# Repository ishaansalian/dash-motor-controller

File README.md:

# 48V BLDC Motor Controller for Dash Robot
Motor control PCB for the Dash humanoid robot project.

## Specs
- 48V nominal input
- 3-phase BLDC motor control
- DRV8323 gate driver
- CAN bus communication
- Based on Ben Katz + mjbots Moteus designs

## Status
🚧 In development - schematic complete, layout in progress

## Hardware
- MCU: STM32F446
- Gate Driver: DRV8323RSRGZT
- MOSFETs: BSC030N08NS5 (80V, 3mΩ)
- Encoder: MA732GQ-Z
- CAN: MCP2542FD

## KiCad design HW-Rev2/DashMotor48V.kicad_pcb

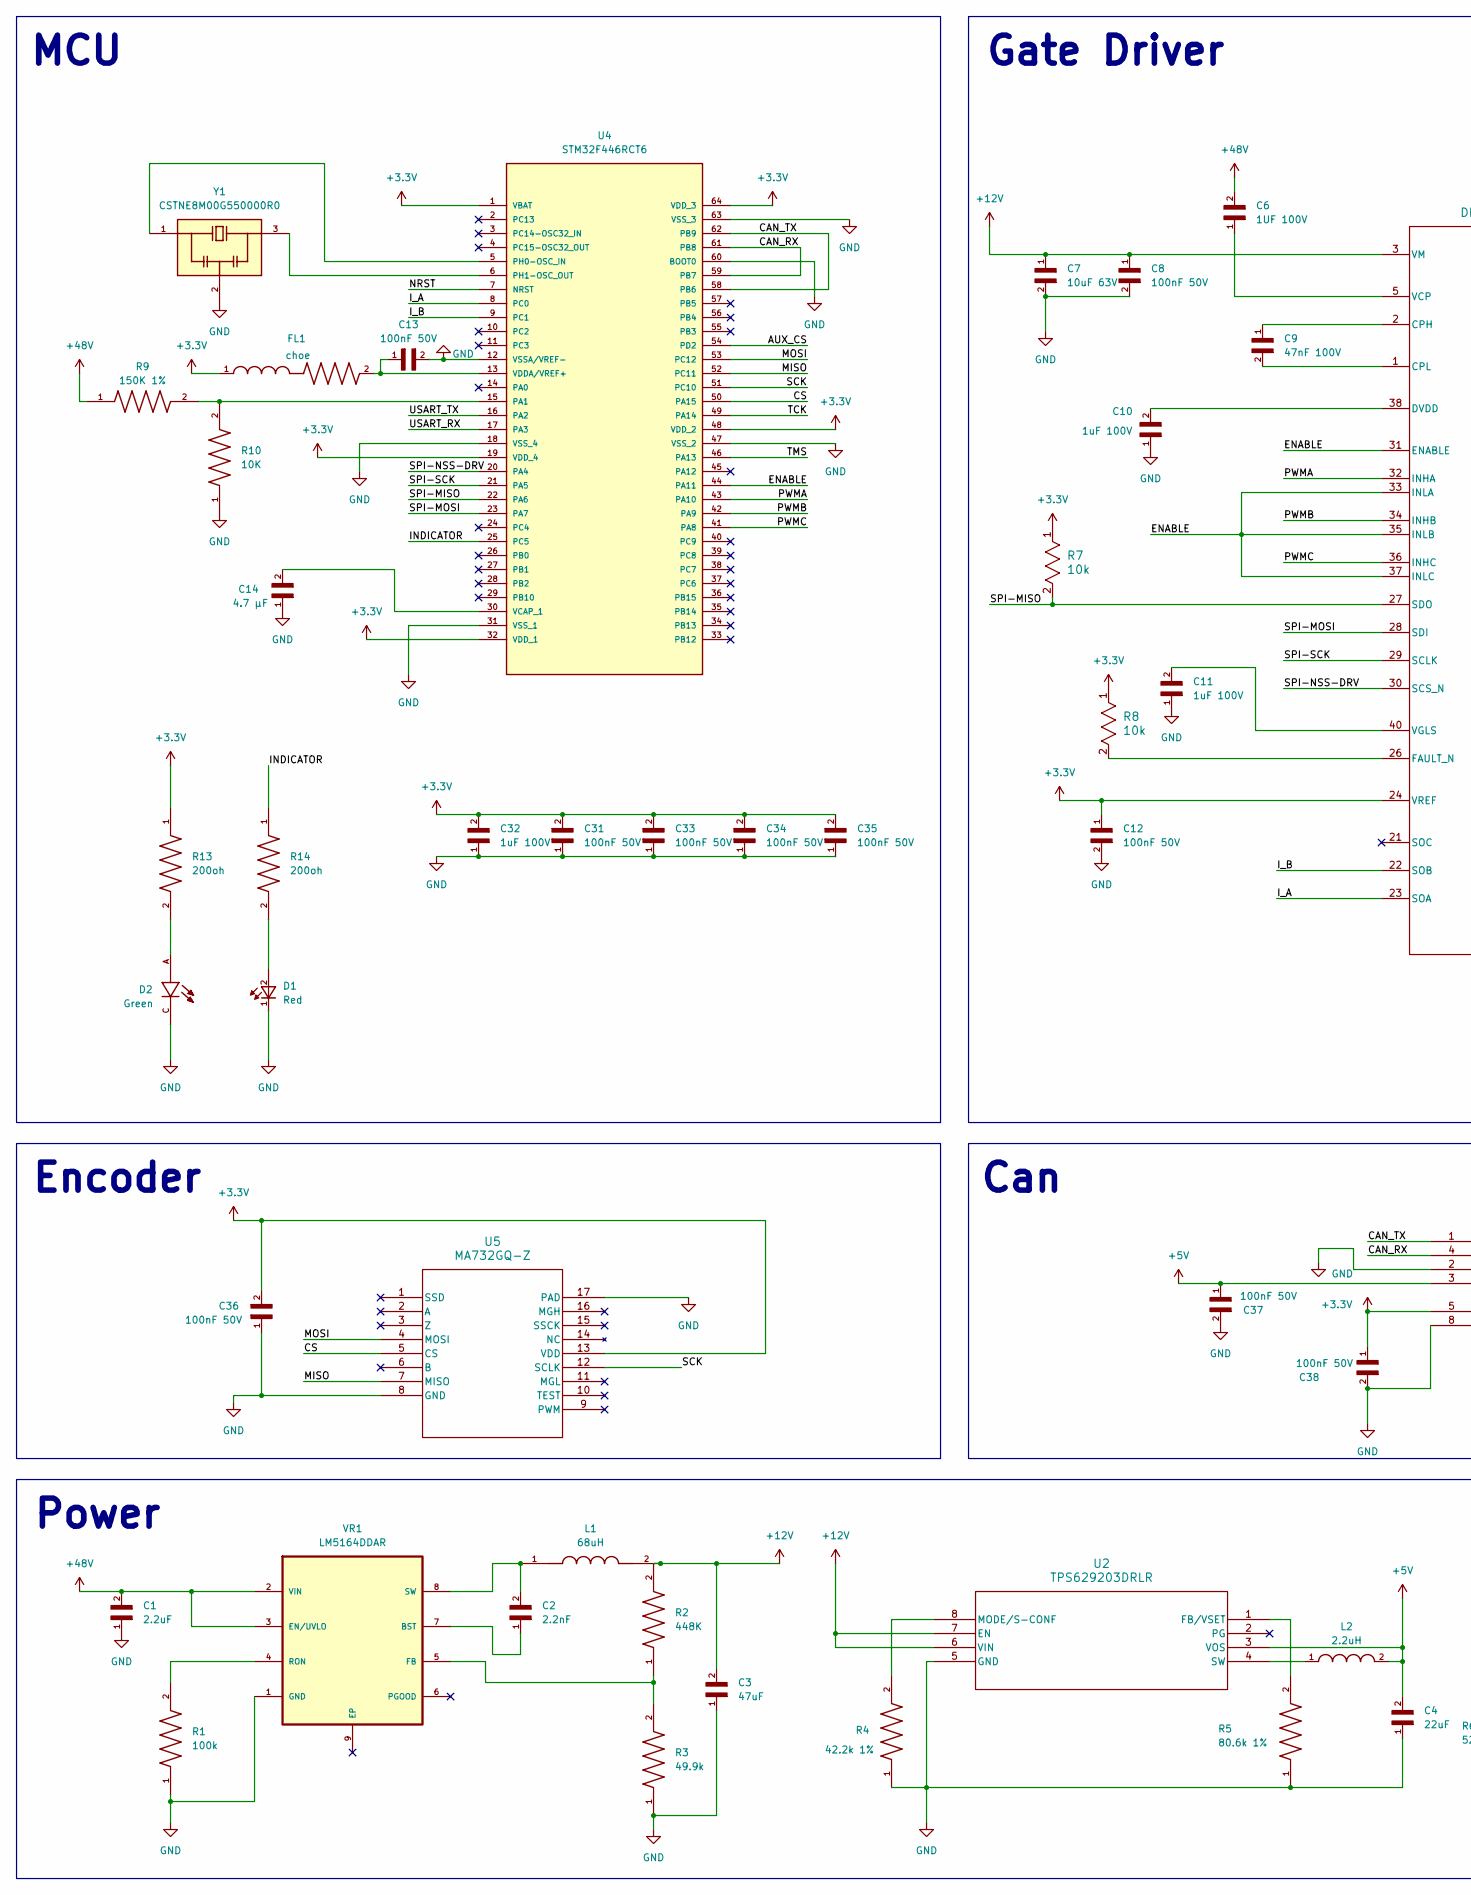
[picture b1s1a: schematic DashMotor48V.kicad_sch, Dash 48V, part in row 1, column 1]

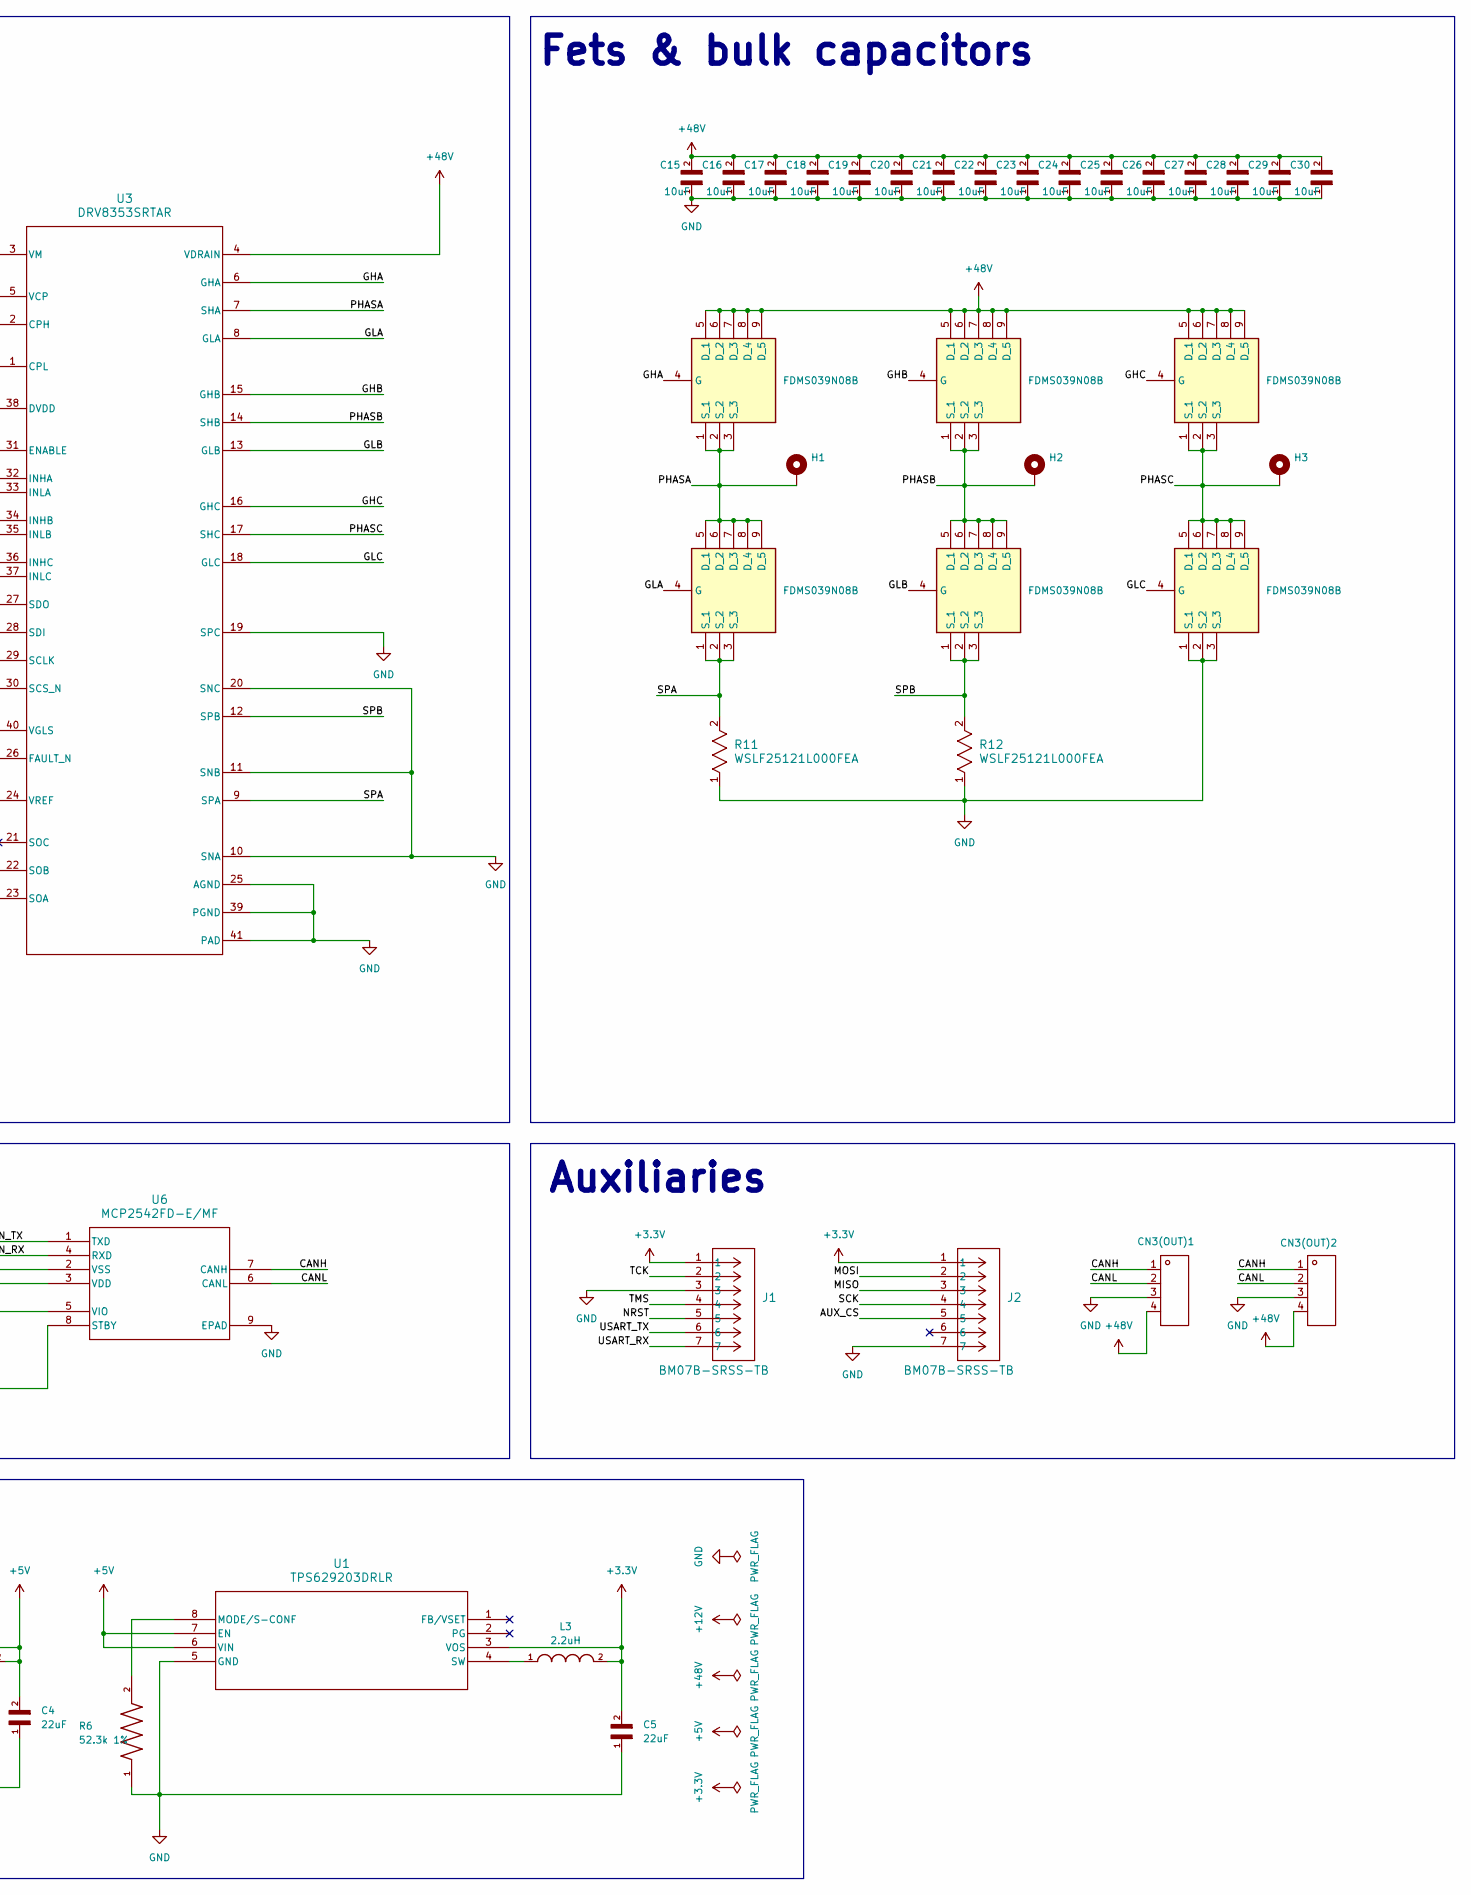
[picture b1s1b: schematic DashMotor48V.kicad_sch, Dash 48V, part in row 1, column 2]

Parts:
C1: 2.2uF; CL31B225KCHSNNE
C2: 2.2nF; CL10B222KB8NNNC
C3: 47uF; GRM31CR61E476ME44L
C4, C5: 22uF; GRM32ER71E226KE15L
C6: 1UF 100V; CL31B105KCHNNNE
C7: 10uF 63V; GRM32ER71J106KA12L
C8, C12, C13, C31, C33, C34, C35, C36, C37, C38: 100nF 50V; CC0603JRX7R9BB104
C9: 47nF 100V; CC0603KRX7R0BB473
C10, C11, C32: 1uF 100V; CL31B105KCHNNNE
C14: 4.7 µF; GRM155R60J475ME87D
C15, C16, C17, C18, C19, C20, C21, C22, C23, C24, C25, C26, C27, C28, C29, C30: 10uF; GRM32EC72A106KE05L
CN3(OUT)1, CN3(OUT)2: XT30(2+2)PB-M.G.B; Manufacturer Part XT30(2+2)PB-M.G.B
D1: Red; LTST_C191KRKT
D2: Green; LTST-C190KGKT
FL1: choe; BLM18AG601SN1D
H1, H2, H3: MountingHole_Pad; MountingHole_2.2mm_M2_Pad
J1, J2: BM07B-SRSS-TB
L1: 68uH; VLS5045EX_680M; PARTREV N/A
L2, L3: 2.2uH; DFE252012PD_2R2M_P2
Q1, Q2, Q3, Q4, Q5, Q6: FDMS039N08B; Manufacturer_Part_Number FDMS039N08B; Mouser Part Number 512-FDMS039N08B
R1: 100k; RC0805FR_07100KL
R2: 448K; RT0603BRD07448KL
R3: 49.9k; RT0603BRD0749K9L
R4: 42.2k 1%; RC0402FR_0742K2L
R5: 80.6k 1%; RC0402FR_0780K6L
R6: 52.3k 1%; RC0402FR_0752K3L
R7, R8: 10k; RC0402FR_0710KL
R9: 150K 1%; RC0402FR_07150KL
R10: 10K; RT0402DRE0710KL
R11, R12: WSLF25121L000FEA
R13, R14: 200oh; RC0402JR-07200RL
U1, U2: TPS629203DRLR
U3: DRV8353SRTAR
U4: STM32F446RCT6
U5: MA732GQ-Z
U6: MCP2542FD-E/MF; MCP2542FD_E_MF
VR1: LM5164DDAR
Y1: CSTNE8M00G550000R0

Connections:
+3.3V: C5.2, C12.1, C31.2, C32.2, C33.2, C34.2, C35.2, C36.2, C38.1, FL1.1, J1.1, J2.1, L3.2, R7.1, R8.1, R13.1, U1.3 (VOS), U3.24 (VREF), U4.1 (VBAT), U4.19 (VDD_4), U4.32 (VDD_1), U4.48 (VDD_2), U4.64 (VDD_3), U5.13 (VDD), U6.5 (VIO)
+5V: C4.2, C37.1, L2.2, U1.6 (VIN), U1.7 (EN), U2.3 (VOS), U6.3 (VDD)
+12V: C3.2, C7.1, C8.1, L1.2, R2.2, U2.6 (VIN), U2.7 (EN), U3.3 (VM)
+48V: C1.2, C6.2, C15.2, C16.2, C17.2, C18.2, C19.2, C20.2, C21.2, C22.2, C23.2, C24.2, C25.2, C26.2, C27.2, C28.2, C29.2, C30.2, CN3(OUT)1.4, CN3(OUT)2.4, Q1.5 (D_1), Q1.6 (D_2), Q1.7 (D_3), Q1.8 (D_4), Q1.9 (D_5), Q3.5 (D_1), Q3.6 (D_2), Q3.7 (D_3), Q3.8 (D_4), Q3.9 (D_5), Q5.5 (D_1), Q5.6 (D_2), Q5.7 (D_3), Q5.8 (D_4), Q5.9 (D_5), R9.1, U3.4 (VDRAIN), VR1.2 (VIN), VR1.3 (EN/UVLO)
/AUX_CS: J2.5, U4.54 (PD2)
/CANH: CN3(OUT)1.1, CN3(OUT)2.1, U6.7 (CANH)
/CANL: CN3(OUT)1.2, CN3(OUT)2.2, U6.6 (CANL)
/CAN_RX: U4.59 (PB7), U4.61 (PB8), U6.4 (RXD)
/CAN_TX: U4.58 (PB6), U4.62 (PB9), U6.1 (TXD)
/CS: U4.50 (PA15), U5.5 (CS)
/ENABLE: U3.31 (ENABLE), U3.33 (INLA), U3.35 (INLB), U3.37 (INLC), U4.44 (PA11)
/GHA: Q1.4 (G), U3.6 (GHA)
/GHB: Q3.4 (G), U3.15 (GHB)
/GHC: Q5.4 (G), U3.16 (GHC)
/GLA: Q2.4 (G), U3.8 (GLA)
/GLB: Q4.4 (G), U3.13 (GLB)
/GLC: Q6.4 (G), U3.18 (GLC)
/INDICATOR: R14.1, U4.25 (PC5)
/I_A: U3.23 (SOA), U4.8 (PC0)
/I_B: U3.22 (SOB), U4.9 (PC1)
/MISO: J2.3, U4.52 (PC11), U5.7 (MISO)
/MOSI: J2.2, U4.53 (PC12), U5.4 (MOSI)
/NRST: J1.5, U4.7 (NRST)
/PHASA: H1.1, Q1.1 (S_1), Q1.2 (S_2), Q1.3 (S_3), Q2.5 (D_1), Q2.6 (D_2), Q2.7 (D_3), Q2.8 (D_4), Q2.9 (D_5), U3.7 (SHA)
/PHASB: H2.1, Q3.1 (S_1), Q3.2 (S_2), Q3.3 (S_3), Q4.5 (D_1), Q4.6 (D_2), Q4.7 (D_3), Q4.8 (D_4), Q4.9 (D_5), U3.14 (SHB)
/PHASC: H3.1, Q5.1 (S_1), Q5.2 (S_2), Q5.3 (S_3), Q6.5 (D_1), Q6.6 (D_2), Q6.7 (D_3), Q6.8 (D_4), Q6.9 (D_5), U3.17 (SHC)
/PWMA: U3.32 (INHA), U4.43 (PA10)
/PWMB: U3.34 (INHB), U4.42 (PA9)
/PWMC: U3.36 (INHC), U4.41 (PA8)
/SCK: J2.4, U4.51 (PC10), U5.12 (SCLK)
/SPA: Q2.1 (S_1), Q2.2 (S_2), Q2.3 (S_3), R11.2, U3.9 (SPA)
/SPB: Q4.1 (S_1), Q4.2 (S_2), Q4.3 (S_3), R12.2, U3.12 (SPB)
/SPI-MISO: R7.2, U3.27 (SDO), U4.22 (PA6)
/SPI-MOSI: U3.28 (SDI), U4.23 (PA7)
/SPI-NSS-DRV: U3.30 (SCS_N), U4.20 (PA4)
/SPI-SCK: U3.29 (SCLK), U4.21 (PA5)
/TCK: J1.2, U4.49 (PA14)
/TMS: J1.4, U4.46 (PA13)
/USART_RX: J1.7, U4.17 (PA3)
/USART_TX: J1.6, U4.16 (PA2)
GND: C1.1, C3.1, C4.1, C5.1, C7.2, C8.2, C10.1, C11.1, C12.2, C13.2, C14.1, C15.1, C16.1, C17.1, C18.1, C19.1, C20.1, C21.1, C22.1, C23.1, C24.1, C25.1, C26.1, C27.1, C28.1, C29.1, C30.1, C31.1, C32.1, C33.1, C34.1, C35.1, C36.1, C37.2, C38.2, CN3(OUT)1.3, CN3(OUT)2.3, D1.1, D2.C, J1.3, J2.7, Q6.1 (S_1), Q6.2 (S_2), Q6.3 (S_3), R1.1, R3.1, R4.1, R5.1, R6.1, R10.1, R11.1, R12.1, U1.5 (GND), U2.5 (GND), U3.10 (SNA), U3.11 (SNB), U3.19 (SPC), U3.20 (SNC), U3.25 (AGND), U3.39 (PGND), U3.41 (PAD), U4.12 (VSSA/VREF-), U4.18 (VSS_4), U4.31 (VSS_1), U4.47 (VSS_2), U4.60 (BOOT0), U4.63 (VSS_3), U5.8 (GND), U5.17 (PAD), U6.2 (VSS), U6.8 (STBY), U6.9 (EPAD), VR1.1 (GND), Y1.2
unnamed: D1.2, R14.2
unnamed: D2.A, R13.2
unnamed: R6.2, U1.8 (MODE/S-CONF)
unnamed: L3.1, U1.4 (SW)
unnamed: R5.2, U2.1 (FB/VSET)
unnamed: R4.2, U2.8 (MODE/S-CONF)
unnamed: L2.1, U2.4 (SW)
unnamed: C9.1, U3.2 (CPH)
unnamed: C9.2, U3.1 (CPL)
unnamed: C10.2, U3.38 (DVDD)
unnamed: R8.2, U3.26 (FAULT_N)
unnamed: C6.1, U3.5 (VCP)
unnamed: C11.2, U3.40 (VGLS)
unnamed: R9.2, R10.2, U4.15 (PA1)
unnamed: U4.5 (PH0-OSC_IN), Y1.1
unnamed: U4.6 (PH1-OSC_OUT), Y1.3
unnamed: C14.2, U4.30 (VCAP_1)
unnamed: C13.1, FL1.2, U4.13 (VDDA/VREF+)
unnamed: C2.1, VR1.7 (BST)
unnamed: R2.1, R3.2, VR1.5 (FB)
unnamed: R1.2, VR1.4 (RON)
unnamed: C2.2, L1.1, VR1.8 (SW)

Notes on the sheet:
MCU
Auxiliaries
Gate Driver
Can
Encoder
Fets & bulk capacitors
Power

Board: 4 copper layers, 79 parts (22 on the bottom side), 63 nets, no tracks yet.

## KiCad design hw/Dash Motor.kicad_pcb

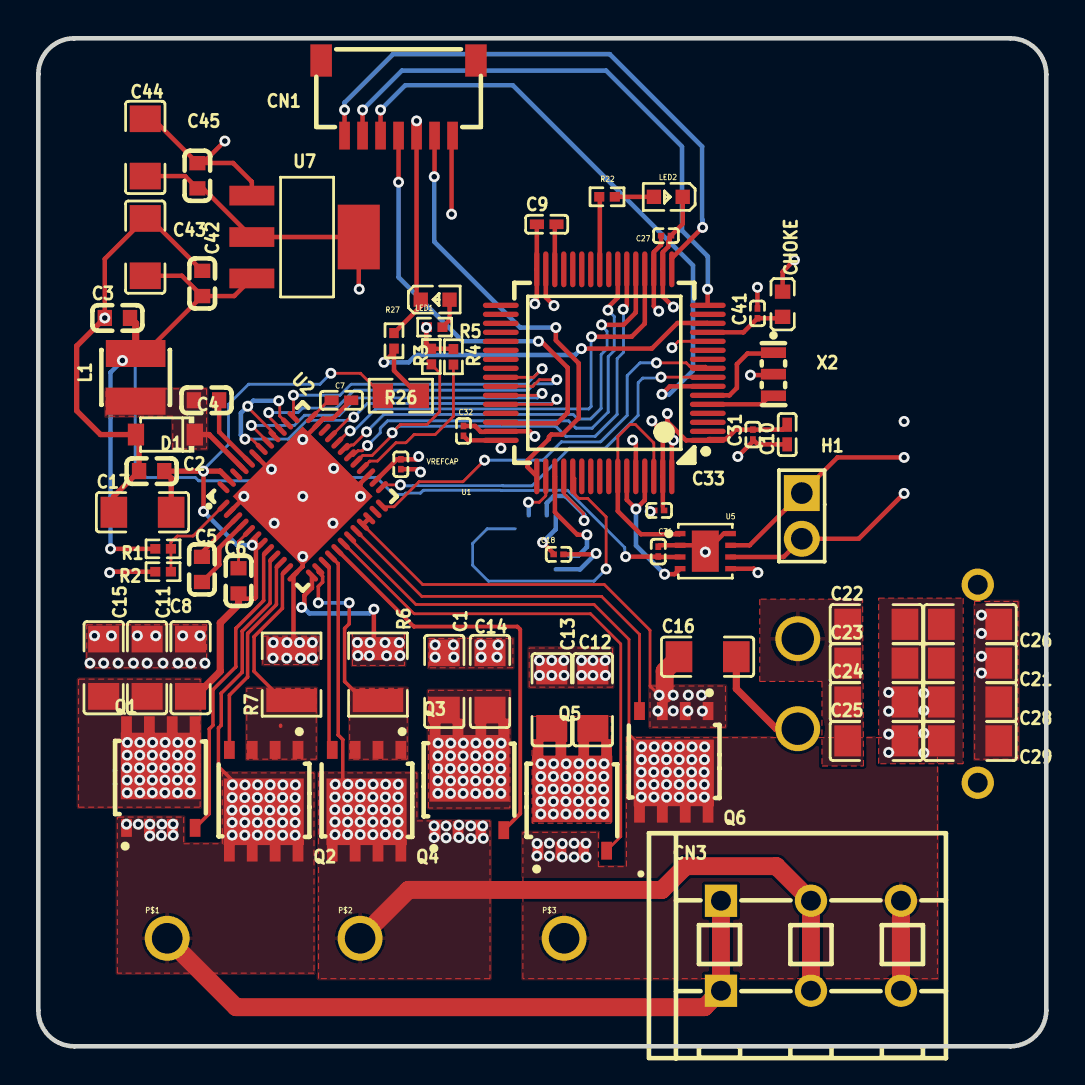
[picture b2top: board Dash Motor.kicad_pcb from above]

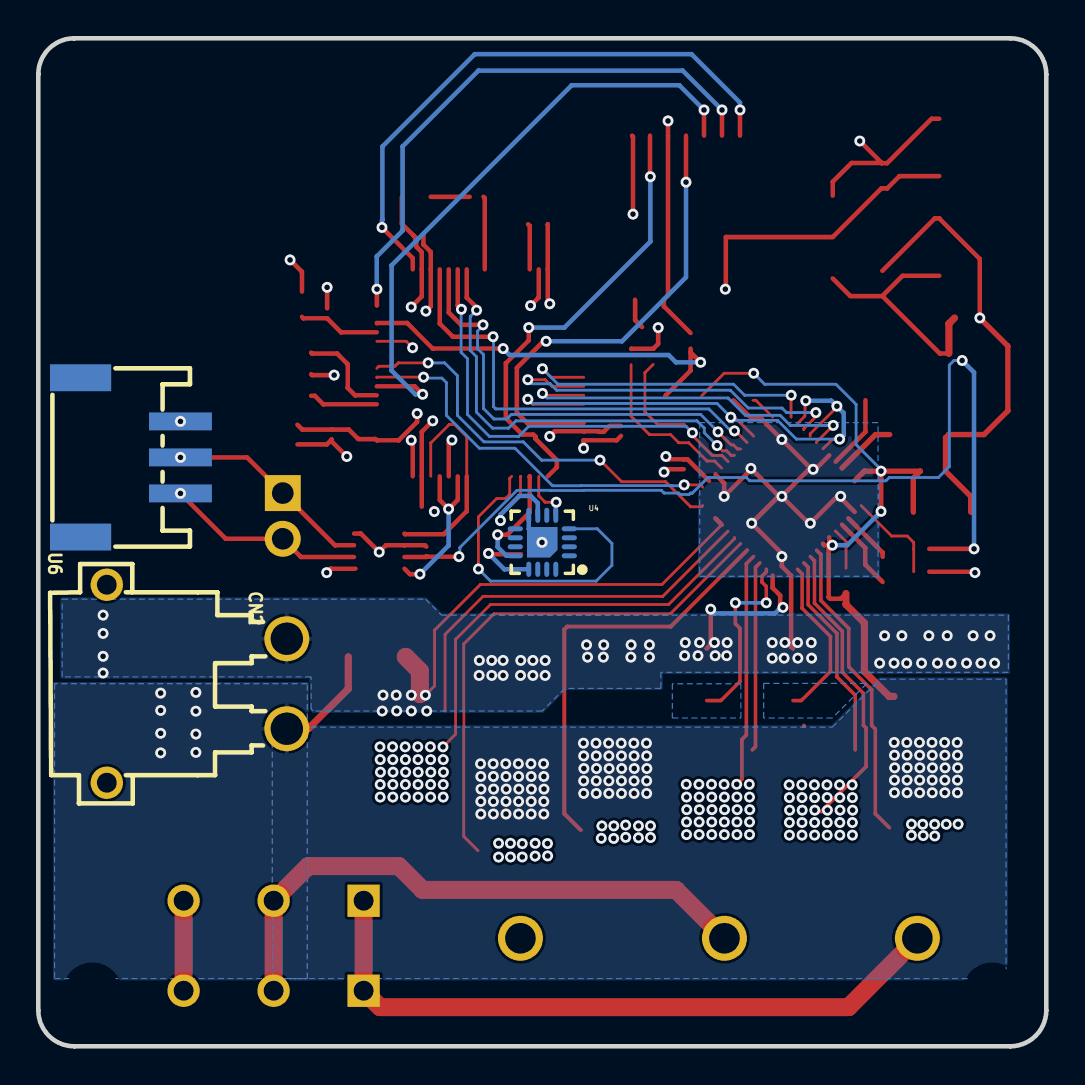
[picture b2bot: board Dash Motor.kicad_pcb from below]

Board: 4 copper layers, 56.0 x 56.0 mm, 72 parts (3 on the bottom side), 54 nets.

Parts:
C1, C8, C11, C12, C13, C14, C15, C16, C17, C21, C22, C23, C24, C25, C26, C28, C29, C43, C44: C1206
C2, C3, C4, C5, C6, C42, C45: C0603
C7, C9, C10: C0402
C18, C27, C31, C32, C33, C34, C41: C0201
CHOKE: L0603
CN1: CONN-SMD_SM07B-SRSS-TB
CN2: CONN-TH_XT30PW-M
CN3: CONN-TH_XY119A-5.0-3P
D1: SOD-123_L2.7-W1.6-LS3.7-RD
H1: HDR-TH_2P-P2.54-V-M
L1: IND-SMD_L3.0-W3.0
LED1, LED2: LED0603-RD
P$1, P$2, P$3: HOLEHOLE
Q1, Q2, Q3, Q4, Q5, Q6: SOP-8_L5.0-W5.0-P1.27-LS6.0_TPH4R008NH-L1Q
R1, R2, R3, R4, R5, R22, R27: R0402
R6, R7: R1210
R26: R0805
U1: LQFP-64_L10.0-W10.0-P0.50-LS12.0-BL
U2: VQFN-48_L7.0-W7.0-P0.50-BL-EP5.5
U4: QFN-16_L3.0-W3.0-P0.50-TL-EP1.7
U5: DFN-8_L3.0-W3.0-P0.65-BL-EP-1
U6: CONN-SMD_S3B-PH-SM4-TB-LF-SN
U7: SOT-223-3_L6.5-W3.4-P2.30-LS7.0-BR
VREFCAP: C0201
X2: OSC-SMD_3P-L3.2-W1.3-P1.20-L

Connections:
3V3: C9.1, C10.2, C18.2, C27.2, C31.2, C32.2, C33.1, C44.1, C45.1, CHOKE.1, CN1.1, R3.2, R4.2, R5.2, U1.1, U1.19, U1.32, U1.48, U1.64, U2.26, U4.13, U5.5, U7.2, U7.4, VREFCAP.2
5V: C3.2, C34.2, C42.2, C43.2, L1.1, R1.2, U5.3, U7.3
24V: C1.2, C2.2, C6.2, C8.2, C11.2, C12.2, C13.2, C14.2, C15.2, C16.2, C17.2, C21.2, C22.2, C23.2, C24.2, C25.2, C26.2, C28.2, C29.2, CN2.2, Q1.5, Q1.6, Q1.7, Q1.8, Q1.9, Q3.5, Q3.6, Q3.7, Q3.8, Q3.9, Q5.5, Q5.6, Q5.7, Q5.8, Q5.9, R26.1, U2.6, U2.7, U2.47
$1N749: U1.5, X2.3
$1N755: U1.6, X2.1
$1N1053: C41.1, CHOKE.2, U1.13
$1N1928: R26.2, R27.2, U1.14
$1N2202: C9.2, U1.30
$1N2494: LED1.2, R5.1
$1N2499: LED2.2, R22.1
$1N13638: R4.1, U2.28
$1N13862: C6.1, U2.5
$1N14164: C4.2, U2.44
$1N14240: R1.1, R2.2, U2.1
$1N14304: C5.2, U2.4
$1N14310: C5.1, U2.3
$1N14320: C7.2, U2.36
CANH: H1.1, U5.7, U6.2
CANL: H1.2, U5.6, U6.3
CAN_RX: U1.59, U1.61, U5.4
CAN_TX: U1.58, U1.62, U5.1
CS: U1.50, U4.5
ENABLE: U1.44, U2.33, U2.38, U2.40, U2.42
GHA: Q1.4, U2.8
GHB: Q3.4, U2.17
GHC: Q5.4, U2.18
GLA: Q2.4, U2.10
GLB: Q4.4, U2.15
GLC: Q6.4, U2.20
GND: C1.1, C2.1, C3.1, C7.1, C8.1, C10.1, C11.1, C12.1, C13.1, C14.1, C15.1, C16.1, C17.1, C18.1, C21.1, C22.1, C23.1, C24.1, C25.1, C26.1, C27.1, C28.1, C29.1, C31.1, C32.1, C33.2, C34.1, C41.2, C42.1, C43.1, C44.2, C45.2, CN1.3, CN2.1, D1.2, LED1.1, LED2.1, Q6.1, Q6.2, Q6.3, R2.1, R6.1, R7.2, R27.1, U1.12, U1.18, U1.31, U1.47, U1.60, U1.63, U2.2, U2.12, U2.13, U2.21, U2.22, U2.27, U2.35, U2.43, U2.49, U4.8, U4.17, U5.2, U5.8, U5.9, U6.1, U7.1, VREFCAP.1, X2.2
INDICATOR: R22.2, U1.25
I_A: U1.8, U2.25
I_B: U1.9, U2.24
MISO: U1.52, U4.7
MOSI: U1.53, U4.4
NRST: CN1.5, U1.7
PHASA: CN3.1, P$1.1, Q1.1, Q1.2, Q1.3, Q2.5, Q2.6, Q2.7, Q2.8, Q2.9, U2.9
PHASB: CN3.2, P$2.1, Q3.1, Q3.2, Q3.3, Q4.5, Q4.6, Q4.7, Q4.8, Q4.9, U2.16
PHASC: CN3.3, P$3.1, Q5.1, Q5.2, Q5.3, Q6.5, Q6.6, Q6.7, Q6.8, Q6.9, U2.19
PWMA: U1.43, U2.41
PWMB: U1.42, U2.39
PWMC: U1.41, U2.37
SCK: U1.51, U4.12
SPA: Q2.1, Q2.2, Q2.3, R7.1, U2.11
SPB: Q4.1, Q4.2, Q4.3, R6.2, U2.14
SPI-MISO: R3.1, U1.22, U2.29
SPI-MOSI: U1.23, U2.30
SPI-NSS-DRV: U1.20, U2.32
SPI-SCK: U1.21, U2.31
SW: C4.1, D1.1, L1.2, U2.45
TCK: CN1.2, U1.49
TMS: CN1.4, U1.46
USART_RX: CN1.7, U1.17
USART_TX: CN1.6, U1.16

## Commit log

2025-11-24 Create Footprints
2025-12-04 Create HW-Rev2
